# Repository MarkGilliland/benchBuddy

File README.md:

# benchBuddy
Code, schematics, and board layouts for the benchBuddy concept.

The benchBuddy is an adjustable power supply, DAQ unit, digital I/O source, and function generator! Just the thing for your workbench - your new buddy

Mark Gilliland 2019

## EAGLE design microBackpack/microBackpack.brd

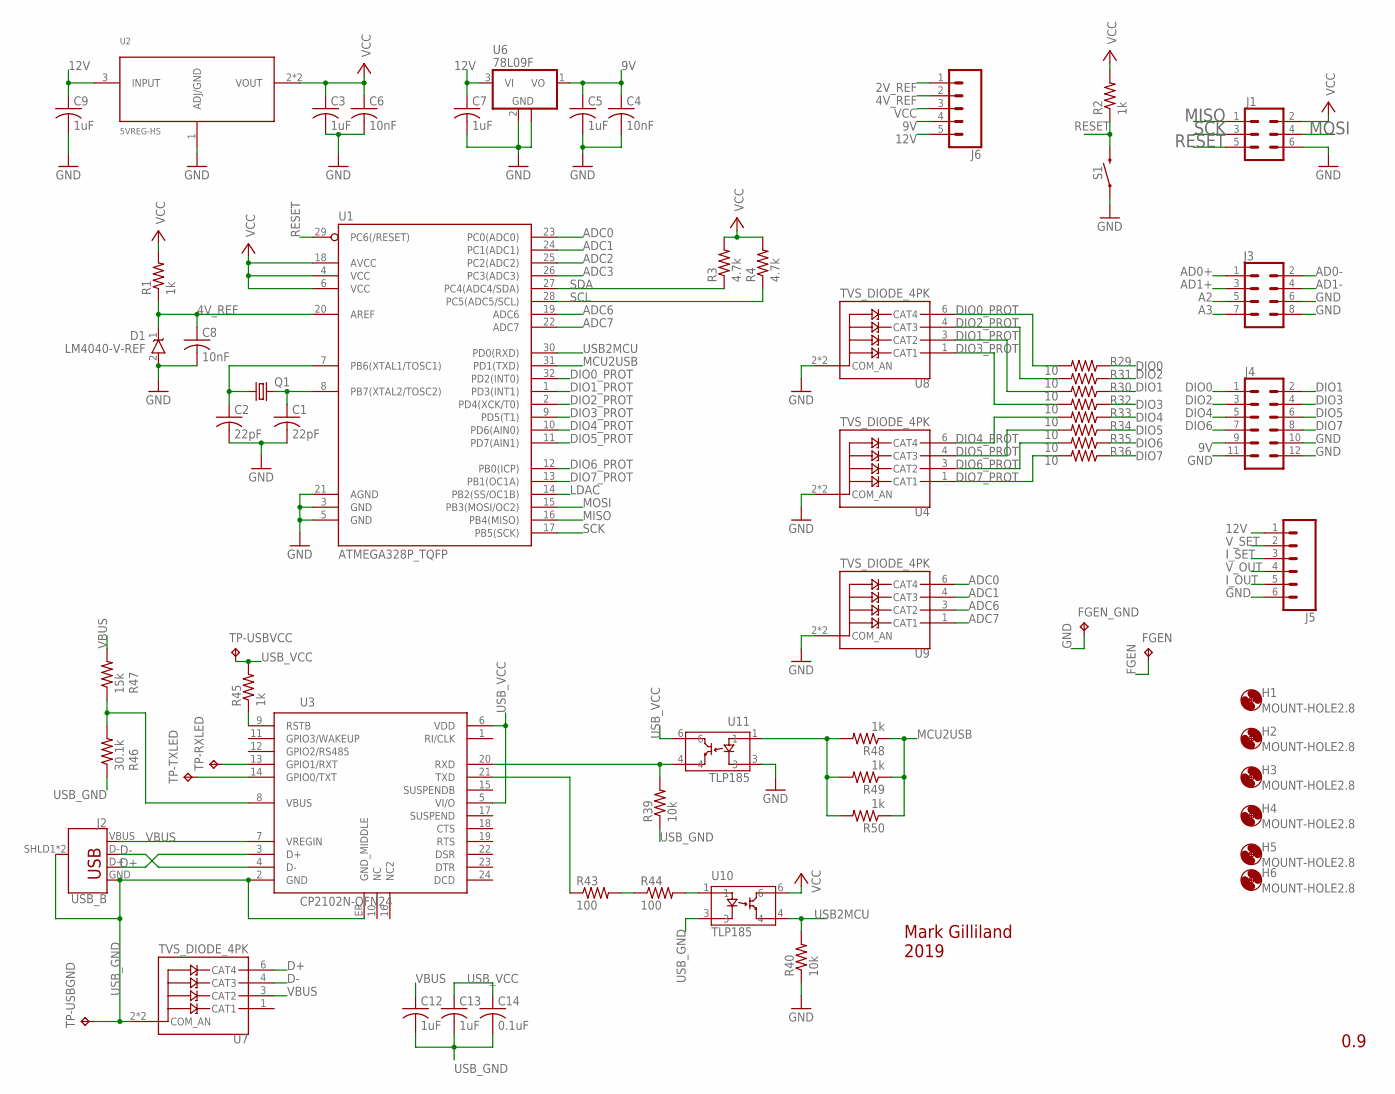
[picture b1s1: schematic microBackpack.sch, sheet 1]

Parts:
C1, C2: 22pF; C0805
C3, C5, C7, C9, C12, C13: 1uF; C0805
C4, C6, C8: 10nF; C0805
C14: 0.1uF; C0805
D1: LM4040-V-REF; SOT23
FGEN: TPPAD1-20Y; P1-20Y
FGEN_GND: TPPAD1-20Y; P1-20Y
H1, H2, H3, H4, H5, H6: MOUNT-HOLE2.8; 2,8
J1: CONN_03X22X3_SILK_MALE_PTH; 2X3
J2: USB_B; USB-B-PTH-VERT
J3: CONN_04X2; 2X4
J4: 2X6 FEMALE; 2X6
J5: CONN_06SILK_FEMALE_PTH; 1X06
J6: CONN_05NO_SILK; 1X05_NO_SILK
Q1: CRYSTALHC49U70; HC49U70
R1, R2, R45, R48, R49, R50: 1k; R0805
R3, R4: 4.7k; R0805
R29, R30, R31, R32, R33, R34, R35, R36: 10; R0805
R39, R40: 10k; R0805
R43, R44: 100; R0603
R46: 30.1k; R0805
R47: 15k; R0805
S1: MOMENTARY-SWITCH-SPST-SMD-5.2-REDUNDANT; TACTILE_SWITCH_SMD_5.2MM
TP-RXLED: TPPAD1-13; P1-13
TP-TXLED: TPPAD1-13; P1-13
TP-USBGND: TPPAD1-13; P1-13
TP-USBVCC: TPPAD1-13; P1-13
U1: ATMEGA328P_TQFP; TQFP32-08
U2: 5VREG-HS; SOT223-HS
U3: CP2102N-QFN24; QFN-24_ALT2
U4, U7, U8, U9: TVS_DIODE_4PK; SOT457
U6: 78L09F; SOT89
U10, U11: TLP185; SO06-4

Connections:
2V_REF: J6.1; also elsewhere on the board
4V_REF: C8.1, D1.1 (+IN), J6.2, R1.1, U1.20 (AREF); also elsewhere on the board
9V: C4.1, C5.1, J4.9, J6.4, U6.1 (VO); also elsewhere on the board
12V: C7.1, C9.1, J5.1, J6.5, U2.3 (INPUT), U6.3 (VI); also elsewhere on the board
A2: J3.5; also elsewhere on the board
A3: J3.7; also elsewhere on the board
AD0+: J3.1; also elsewhere on the board
AD0-: J3.2; also elsewhere on the board
AD1+: J3.3; also elsewhere on the board
AD1-: J3.4; also elsewhere on the board
ADC0: U1.23 (PC0(ADC0)), U9.6 (CAT4); also elsewhere on the board
ADC1: U1.24 (PC1(ADC1)), U9.4 (CAT3); also elsewhere on the board
ADC2: U1.25 (PC2(ADC2)); also elsewhere on the board
ADC3: U1.26 (PC3(ADC3)); also elsewhere on the board
ADC6: U1.19 (ADC6), U9.3 (CAT2); also elsewhere on the board
ADC7: U1.22 (ADC7), U9.1 (CAT1); also elsewhere on the board
CRYS_N: C2.1, Q1.1, U1.7 (PB6(XTAL1/TOSC1))
CRYS_P: C1.1, Q1.2, U1.8 (PB7(XTAL2/TOSC2))
D+: J2.D+, U3.3 (D+), U7.6 (CAT4)
D-: J2.D-, U3.4 (D-), U7.4 (CAT3)
DIO0: J4.1, R29.1
DIO0_PROT: R29.2, U1.32 (PD2(INT0)), U8.6 (CAT4)
DIO1: J4.2, R30.1
DIO1_PROT: R30.2, U1.1 (PD3(INT1)), U8.3 (CAT2)
DIO2: J4.3, R31.1
DIO2_PROT: R31.2, U1.2 (PD4(XCK/T0)), U8.4 (CAT3)
DIO3: J4.4, R32.1
DIO3_PROT: R32.2, U1.9 (PD5(T1)), U8.1 (CAT1)
DIO4: J4.5, R33.1
DIO4_PROT: R33.2, U1.10 (PD6(AIN0)), U4.6 (CAT4)
DIO5: J4.6, R34.1
DIO5_PROT: R34.2, U1.11 (PD7(AIN1)), U4.4 (CAT3)
DIO6: J4.7, R35.1
DIO6_PROT: R35.2, U1.12 (PB0(ICP)), U4.3 (CAT2)
DIO7: J4.8, R36.1
DIO7_PROT: R36.2, U1.13 (PB1(OC1A)), U4.1 (CAT1); also elsewhere on the board
FGEN: FGEN.TP; also elsewhere on the board
GND: C1.2, C2.2, C3.2, C4.2, C5.2, C6.2, C7.2, C8.2, C9.2, D1.2 (-IN), FGEN_GND.TP, J1.6, J3.6, J3.8, J4.10, J4.11, J4.12, J5.6, R40.1, S1.1, S1.2 (1), U1.3 (GND), U1.5 (GND), U1.21 (AGND), U2.1 (ADJ/GND), U4.2 (COM_AN), U4.5 (COM_AN), U6.2 (GND), U6.2@1 (GND), U8.2 (COM_AN), U8.5 (COM_AN), U9.2 (COM_AN), U9.5 (COM_AN), U11.3; also elsewhere on the board
I_OUT: J5.5; also elsewhere on the board
I_SET: J5.3; also elsewhere on the board
LDAC: U1.14 (PB2(SS/OC1B)); also elsewhere on the board
MCU2USB: R48.1, R49.1, R50.1, U1.31 (PD1(TXD))
MISO: J1.1, U1.16 (PB4(MISO))
MOSI: J1.4, U1.15 (PB3(MOSI/OC2))
unnamed: R48.2, R49.2, R50.2, U11.1
unnamed: R46.2, R47.1, U3.8 (VBUS)
unnamed: R44.2, U10.1
unnamed: R39.2, U3.20 (RXD), U11.4
unnamed: R43.2, R44.1
unnamed: R43.1, U3.21 (TXD)
unnamed: TP-RXLED.TP, U3.13 (GPIO1/RXT)
unnamed: TP-TXLED.TP, U3.14 (GPIO0/TXT)
unnamed: R45.1, U3.9 (RSTB)
RESET: J1.5, R2.1, S1.3 (2), S1.4 (2), U1.29 (PC6(/RESET))
SCK: J1.3, U1.17 (PB5(SCK))
SCL: R4.1, U1.28 (PC5(ADC5/SCL)); also elsewhere on the board
SDA: R3.1, U1.27 (PC4(ADC4/SDA)); also elsewhere on the board
USB2MCU: R40.2, U1.30 (PD0(RXD)), U10.4
USB_GND: C12.2, C13.2, C14.2, J2.GND, J2.SHLD1 (SHIELD), J2.SHLD2 (SHIELD), R39.1, R46.1, TP-USBGND.TP, U3.2 (GND), U3.EP (GND_MIDDLE), U7.2 (COM_AN), U7.5 (COM_AN), U10.3
USB_VCC: C13.1, C14.1, R45.2, TP-USBVCC.TP, U3.5 (VI/O), U3.6 (VDD), U11.6
VBUS: C12.1, J2.VBUS, R47.2, U3.7 (VREGIN), U7.3 (CAT2)
VCC: C3.1, C6.1, J1.2, J6.3, R1.2, R2.2, R3.2, R4.2, U1.4 (VCC), U1.6 (VCC), U1.18 (AVCC), U2.2 (VOUT), U2.4 (VOUT), U10.6; also elsewhere on the board
V_OUT: J5.4; also elsewhere on the board
V_SET: J5.2; also elsewhere on the board

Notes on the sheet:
Mark Gilliland 2019
0.9

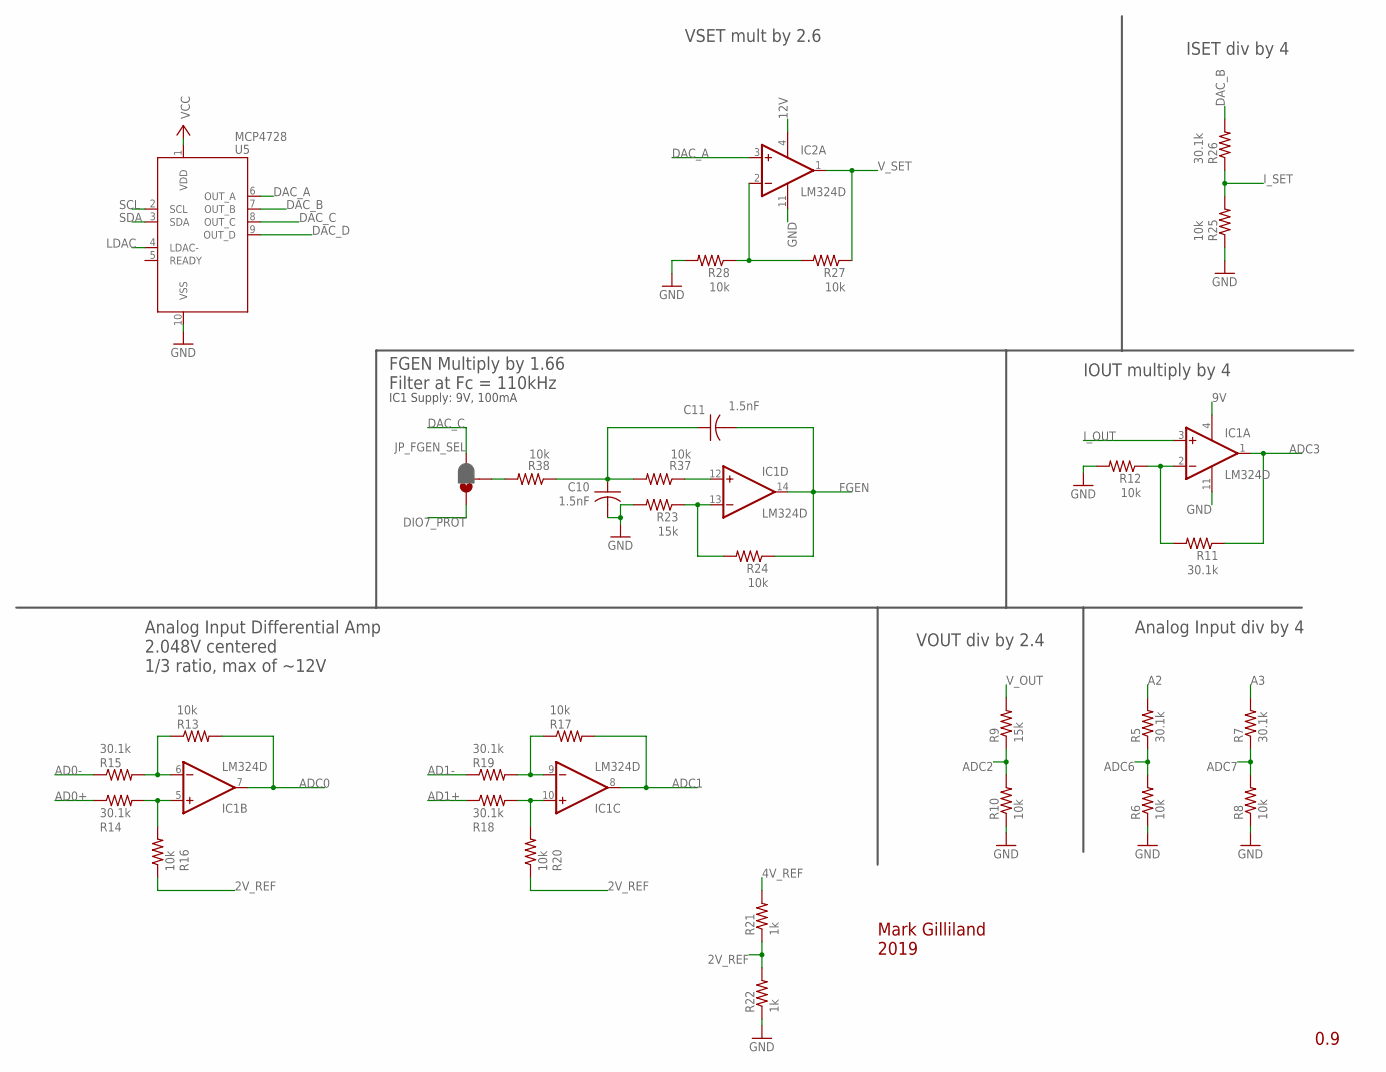
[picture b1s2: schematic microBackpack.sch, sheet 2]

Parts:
C10, C11: 1.5nF; C0805
IC1, IC2: LM324D; SO14
JP_FGEN_SEL: JUMPER-SMT_3_1-NC_PASTE_SILK; SMT-JUMPER_3_1-NC_PASTE_SILK
R5, R7, R11, R14, R15, R18, R19, R26: 30.1k; R0805
R6, R8, R10, R12, R13, R16, R17, R20, R24, R25, R27, R28, R37, R38: 10k; R0805
R9, R23: 15k; R0805
R21, R22: 1k; R0805
U5: MCP4728; MSOP10

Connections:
2V_REF: R16.1, R20.1, R21.1, R22.2; also elsewhere on the board
4V_REF: R21.2; also elsewhere on the board
9V: IC1.4 (V+); also elsewhere on the board
12V: IC2.4 (V+); also elsewhere on the board
A2: R5.2; also elsewhere on the board
A3: R7.2; also elsewhere on the board
AD0+: R14.1; also elsewhere on the board
AD0-: R15.1; also elsewhere on the board
AD1+: R18.1; also elsewhere on the board
AD1-: R19.1; also elsewhere on the board
ADC0: IC1.7 (OUT), R13.2; also elsewhere on the board
ADC1: IC1.8 (OUT), R17.2; also elsewhere on the board
ADC2: R9.1, R10.2; also elsewhere on the board
ADC3: IC1.1 (OUT), R11.1; also elsewhere on the board
ADC6: R5.1, R6.2; also elsewhere on the board
ADC7: R7.1, R8.2; also elsewhere on the board
DAC_A: IC2.3 (+IN), U5.6 (OUT_A)
DAC_B: R26.2, U5.7 (OUT_B)
DAC_C: JP_FGEN_SEL.3, U5.8 (OUT_C)
DAC_D: U5.9 (OUT_D)
DIO7_PROT: JP_FGEN_SEL.1; also elsewhere on the board
FGEN: C11.2, IC1.14 (OUT), R24.1; also elsewhere on the board
GND: C10.2, IC1.11 (V-), IC2.11 (V-), R6.1, R8.1, R10.1, R12.2, R22.1, R23.2, R25.1, R28.2, U5.10 (VSS); also elsewhere on the board
I_OUT: IC1.3 (+IN); also elsewhere on the board
I_SET: R25.2, R26.1; also elsewhere on the board
LDAC: U5.4 (LDAC-); also elsewhere on the board
unnamed: JP_FGEN_SEL.2, R38.2
unnamed: IC1.13 (-IN), R23.1, R24.2
unnamed: C10.1, C11.1, R37.2, R38.1
unnamed: IC1.2 (-IN), R11.2, R12.1
unnamed: IC1.6 (-IN), R13.1, R15.2
unnamed: IC1.5 (+IN), R14.2, R16.2
unnamed: IC2.2 (-IN), R27.2, R28.1
unnamed: IC1.12 (+IN), R37.1
unnamed: IC1.9 (-IN), R17.1, R19.2
unnamed: IC1.10 (+IN), R18.2, R20.2
SCL: U5.2 (SCL); also elsewhere on the board
SDA: U5.3 (SDA); also elsewhere on the board
VCC: U5.1 (VDD); also elsewhere on the board
V_OUT: R9.2; also elsewhere on the board
V_SET: IC2.1 (OUT), R27.1; also elsewhere on the board

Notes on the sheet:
Mark Gilliland 2019
0.9
VOUT div by 2.4
IOUT multiply by 4
Analog Input div by 4
Analog Input Differential Amp 2.048V centered 1/3 ratio, max of ~12V
FGEN Multiply by 1.66 Filter at Fc = 110kHz
IC1 Supply: 9V, 100mA
ISET div by 4
VSET mult by 2.6

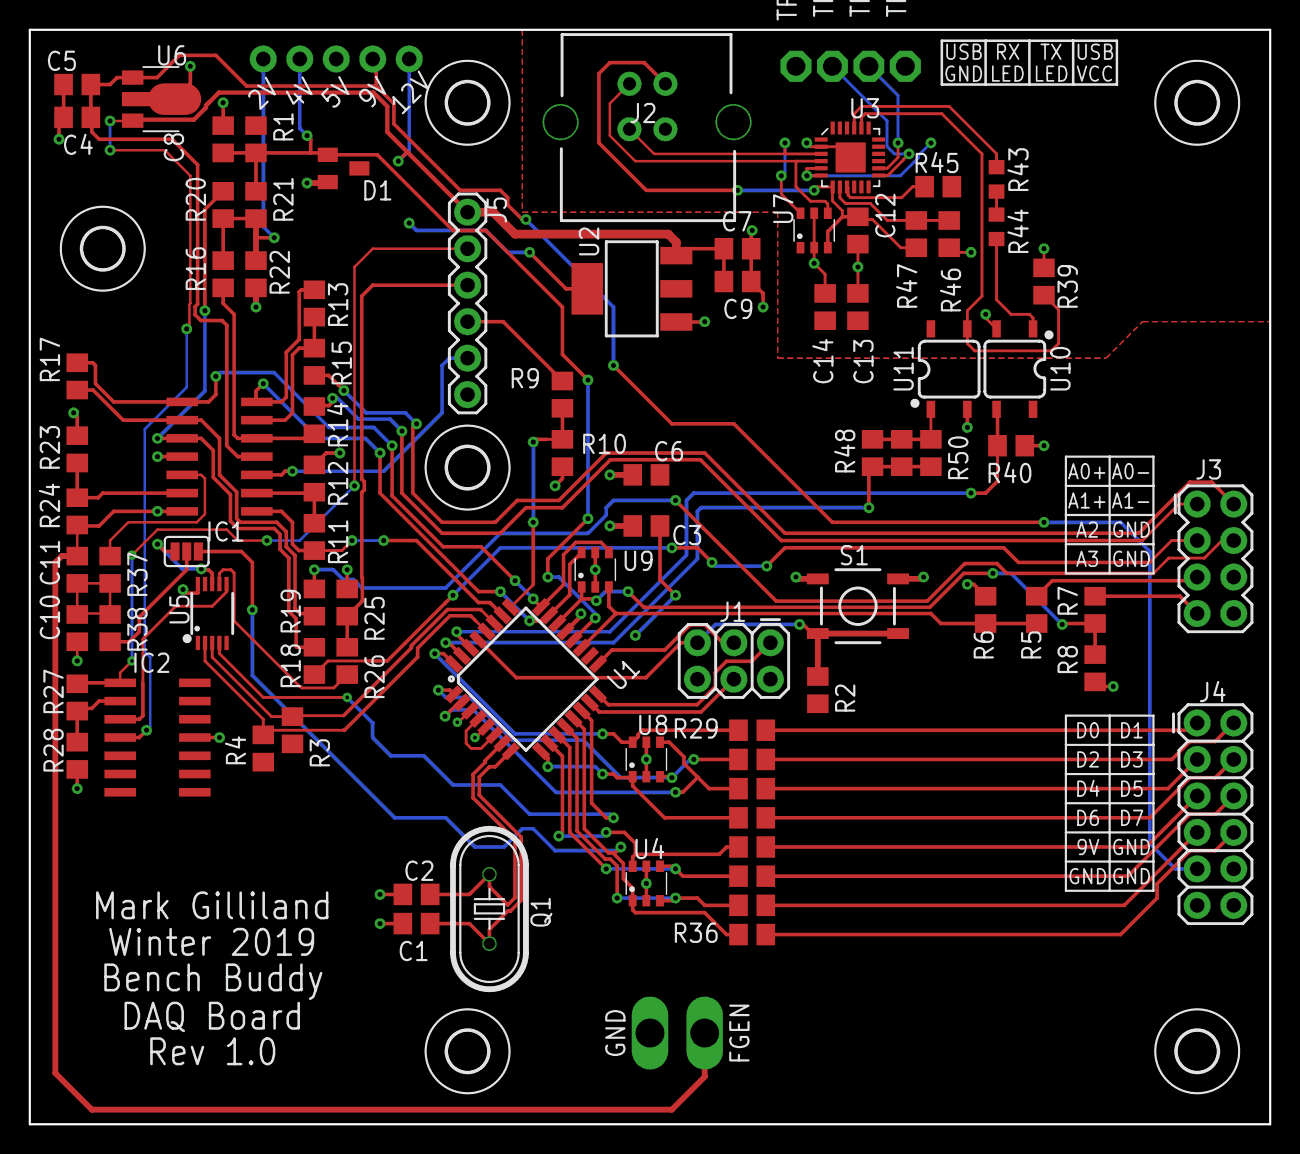
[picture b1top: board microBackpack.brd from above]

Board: 2 copper layers, 86.4 x 76.2 mm, 97 parts (0 on the bottom side), 77 nets.

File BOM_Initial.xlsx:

Usage | Component Type | RefDes | Value | Package | Description | Part Number 1 | Part Number 2 | Link | Qty Required | Order Qty | Price Per | Price | Board | Part List
Crystal Capacitors | Passive, Capacitor | C1, C2 | 22pF | C0805 | CAP CER 22PF 16V C0G/NP0 0805 | 732-7816-1-ND |  | 732-7816-1-ND | 2 | 10 | 4.2999999999999997E-2 | 8.5999999999999993E-2 | MBP | MBP-C1, C2
FGen Filter Caps | Passive, Capacitor | C10, C11 | 1.5nF | C0805 | CAP CER 1500PF 25V NP0 0805 | 732-12256-1-ND |  | 732-12256-1-ND | 2 | 2 | 0.1 | 0.2 | MBP | MBP-C10, C11
Power Filter Caps | Passive, Capacitor | C3, C5, C7, C9 | 1uF | C0805 |  | 1276-6471-1-ND |  | 1276-6471-1-ND | 4 | 10 | 4.7E-2 | 0.188 | MBP | MBP-C3, C5, C7, C9
Power Filter Caps | Passive, Capacitor | C4, C6, C8 | 10nF | C0805 |  | ‎732-8074-1-ND‎ |  | ‎732-8074-1-ND‎ | 3 | 10 | 3.4000000000000002E-2 | 0.10200000000000001 | MBP | MBP-C4, C6, C8
Filter Cap, HF | Passive, Capacitor | C8, C11, C13 | 0.1uF | C0805 |  | 1276-1007-1-ND |  | 1276-1007-1-ND | 3 | 10 | 0.04 | 0.12 | PSB | PSB-C8, C11, C13
Filter Cap, LF | Passive, Capacitor | C9, C10, C12, C14 | 10uF | C0805 |  | 1276-6455-1-ND |  | 1276-6455-1-ND | 4 | 10 | 0.108 | 0.432 | PSB | PSB-C9, C10, C12, C14
Voltage Reference | Diode | D1 | SOT-23-3 |  |  | 576-1048-1-ND |  | 576-1048-1-ND | 1 | 1 | 0.28999999999999998 | 0.28999999999999998 | MBP | MBP-D1
4A Fuse for 12V | Fuse, PTC | F1 |  | F1812 | PTC RESET FUSE 16V 2.6A 1812 | 507-1780-1-ND |  | 507-1780-1-ND | 1 | 2 | 0.28000000000000003 | 0.28000000000000003 | PSB | PSB-F1
750mA Fuse for 3.3 and 5V | Fuse, PTC | F2, F3 |  | F1812 | PTC RESET FUSE 16V 500MA 1812 | 507-1761-1-ND |  | 507-1761-1-ND | 2 | 3 | 0.14000000000000001 | 0.28000000000000003 | PSB | PSB-F2, F3
1A Fuse for 3.3 and 5V, alternate part | Fuse, PTC | F2, F3 |  | F1812 | PTC RESET FUSE 16V 750MA 1812 | 507-1763-1-ND |  | 507-1763-1-ND | 2 | 3 | 0.14000000000000001 | 0.28000000000000003 | PSB | PSB-F2, F3
Op Amp for AINs | IC, Linear | IC1, IC2 | SO14 |  |  | LM324DR2GOSCT-ND |  | LM324DR2GOSCT-ND | 2 | 2 | 0.35 | 0.7 | MBP | MBP-IC1, IC2
ICSP Header | Header | J1 |  |  | 2x3 0.1" header, for flashing the bootloader to the atmega | 2057-PH2-06-UA-ND |  | 2057-PH2-06-UA-ND | 1 | 1 | 0.12 | 0.12 | MBP | MBP-J1
USB Port | Header | J2 |  |  | USB TYPE B, RIGHT ANGLE, WHITE C | 2057-USB-B-S-RA-WT-SPCC-ND |  | 2057-USB-B-S-RA-WT-SPCC-ND | 1 | 1 | 0.45 | 0.45 | MBP | MBP-J2
USB Port, Vertical | Header | J2 |  |  | CONN RCPT USB2.0 TYPEB 4POS VERT | 102-4000-ND |  | 102-4000-ND | 1 | 1 | 0.75 | 0.75 | MBP | MBP-J2
Expansion Header, Male | Header | J3 |  | 1x6x0.1" |  | 2057-PH1-06-UA-ND |  | 2057-PH1-06-UA-ND | 1 | 1 | 0.12 | 0.12 | PSB | PSB-J3
Output Header, DIO | Header | J4, J3 |  |  | 6x2 header, 0.1", for digitals | 2057-PH2-12-UA-ND |  | 2057-PH2-12-UA-ND | 2 | 2 | 0.18 | 0.36 | MBP | MBP-J4, J3
Expansion Header, Female | Header | J5 |  | 1x6x0.1" |  | S7039-ND |  | S7039-ND | 1 | 1 | 0.53 | 0.53 | MBP | MBP-J5
UART Optoisolator | IC, Logic | NA | 6-SOIC |  |  | TLP185(GB-TPLSECT-ND |  | TLP185(GB-TPLSECT-ND | 2 | 2 | 0.42 | 0.84 | MBP | MBP-NA
5W 5V Switch Mode Reg | IC, DCDC Converter | PS1, PS2 |  | 3-SIP Module | 5V 1.0A DC-DC NON-ISOLATED | 102-5018-ND |  | 102-5018-ND | 2 | 2 | 2.96 | 5.92 | PSB | PSB-PS1, PS2
Crystal Oscillator | Crystal | Q1 |  | HC-49 | 16MHz | 887-2015-ND |  | 887-2015-ND | 1 | 1 | 0.3 | 0.3 | MBP | MBP-Q1
Vref Resistor | Passive, Resistor | R1, R2, R21, R22 | 1k | R0805 | RES 1K OHM 1% 1/8W 0805 | RMCF0805FT1K00CT-ND |  | RMCF0805FT1K00CT-ND | 4 | 10 | 2.7E-2 | 0.108 | MBP | MBP-R1, R2, R21, R22
DIO Protection resistors | Passive, Resistor | R29, R30, R31, R32, R33, R34, R35, R36 | 10 | R0805 | RES SMD 10 OHM 5% 1/8W 0805 | CR0805-JW-100ELFCT-ND |  | CR0805-JW-100ELFCT-ND | 8 | 10 | 1.7999999999999999E-2 | 0.14399999999999999 | MBP | MBP-R29, R30, R31, R32, R33, R34, R35, R36
I2C Pull-ups | Passive, Resistor | R3, R4 | 4.7k | R0805 | RES SMD 4.7K OHM 5% 1/8W 0805 | CR0805-JW-472ELFCT-ND |  | CR0805-JW-472ELFCT-ND | 2 | 10 | 1.7999999999999999E-2 | 3.5999999999999997E-2 | MBP | MBP-R3, R4
12V LED Resistor | Passive, Resistor | R31 | 1.2k | R1206 | RES 1.2K OHM 5% 1/4W 1206 | RMCF1206JT1K20CT-ND |  | RMCF1206JT1K20CT-ND | 1 | 1 | 0.1 | 0.1 | PSB | PSB-R31
5V LED Resistor | Passive, Resistor | R32 | 390Ω | R1206 | RES 390 OHM 5% 1/4W 1206 | RMCF1206JT390RCT-ND |  | RMCF1206JT390RCT-ND | 1 | 1 | 0.1 | 0.1 | PSB | PSB-R32
3.3V LED Resistor | Passive, Resistor | R33 | 150Ω | R1206 | RES 150 OHM 5% 1/4W 1206 | RMCF1206JT150RCT-ND |  | RMCF1206JT150RCT-ND | 1 | 1 | 0.1 | 0.1 | PSB | PSB-R33
Amp Resistors | Passive, Resistor | R5, R7, R11, R14, R15, R18, R19, R26 | 30.1k 1% | R0805 | RES 30.1K OHM 1% 1/8W 0805 | RMCF0805FT30K1CT-ND |  | RMCF0805FT30K1CT-ND | 8 | 10 | 2.7E-2 | 0.216 | MBP | MBP-R5, R7, R11, R14, R15, R18, R19, R26
Amp Resistors | Passive, Resistor | R6, R8, R10, R12, R13, R16, R17, R20, R24, R25, R27, R28, R37, R38 | 10k 1% | R0805 | RES 10K OHM 1% 1/8W 0805 | RMCF0805FT10K0CT-ND |  | RMCF0805FT10K0CT-ND | 14 | 100 | 2.7E-2 | 0.378 | MBP | MBP-R6, R8, R10, R12, R13, R16, R17, R20, R24, R25, R27, R28, R37, R38
Amp Resistors | Passive, Resistor | R9, R23 | 15k 1% | R0805 | RES 15K OHM 1% 1/8W 0805 | RMCF0805FT15K0CT-ND |  | RMCF0805FT15K0CT-ND | 2 | 10 | 2.7E-2 | 5.3999999999999999E-2 | MBP | MBP-R9, R23
Reset button | Button | S1 |  | 5.2mm sqaure | TACT 5.2 X 5.2, 1.5 MM H, 160GF, | CKN12220-1-ND |  | CKN12220-1-ND | 1 | 1 | 0.1 | 0.1 | MBP | MBP-S1
Selection Switch | Switch | S3 |  |  | Made to match ones from class | 401-2001-ND |  | 401-2001-ND | 1 | 1 | 0.43 | 0.43 | PSB | PSB-S3
Microcontroller, Arduino | IC, Logic | U1 |  | 32-TQFP |  | ATMEGA328PB-AURCT-ND | ATMega328P | ATMEGA328PB-AURCT-ND | 1 | 1 | 1.42 | 1.42 | MBP | MBP-U1
5V Supply | IC, Linear | U2 |  | SOT223 | IC REG LINEAR 5V 800MA SOT223 | AZ1117IH-5.0TRG1DICT-ND |  | AZ1117IH-5.0TRG1DICT-ND | 1 | 3 | 0.36 | 0.36 | MBP | MBP-U2
1A 3.3V Linear Reg | IC, Volt Reg | U3 |  | SOT223 | IC REG LINEAR 3.3V 1A SOT223 | AP2114HA-3.3TRG1DICT-ND |  | AP2114HA-3.3TRG1DICT-ND | 1 | 3 | 0.36 | 0.36 | PSB | PSB-U3
USB to UART Adapter | IC, Logic | U3 |  |  | CP2102N-A02-GQFN24R | 336-5888-1-ND |  | 336-5888-1-ND | 1 | 1 | 1.35 | 1.35 | MBP | MBP-U3
5V/AIN/USB protection diodes | Diode | U4, U7, U8, U9 |  |  |  | 1727-1582-1-ND |  | 1727-1582-1-ND | 4 | 5 | 0.31 | 1.24 | MBP | MBP-U4, U7, U8, U9
Op Amp Power Supply | IC, Linear | U6 | SOT89-3 |  | IC REG LINEAR 9V 100MA SOT89-3 | 497-1192-1-ND | L78L09ACUTR | 497-1192-1-ND | 1 | 1 | 0.4 | 0.4 | MBP | MBP-U6
 |  |  |  |  |  |  |  |  |  |  | Total: | 19.244

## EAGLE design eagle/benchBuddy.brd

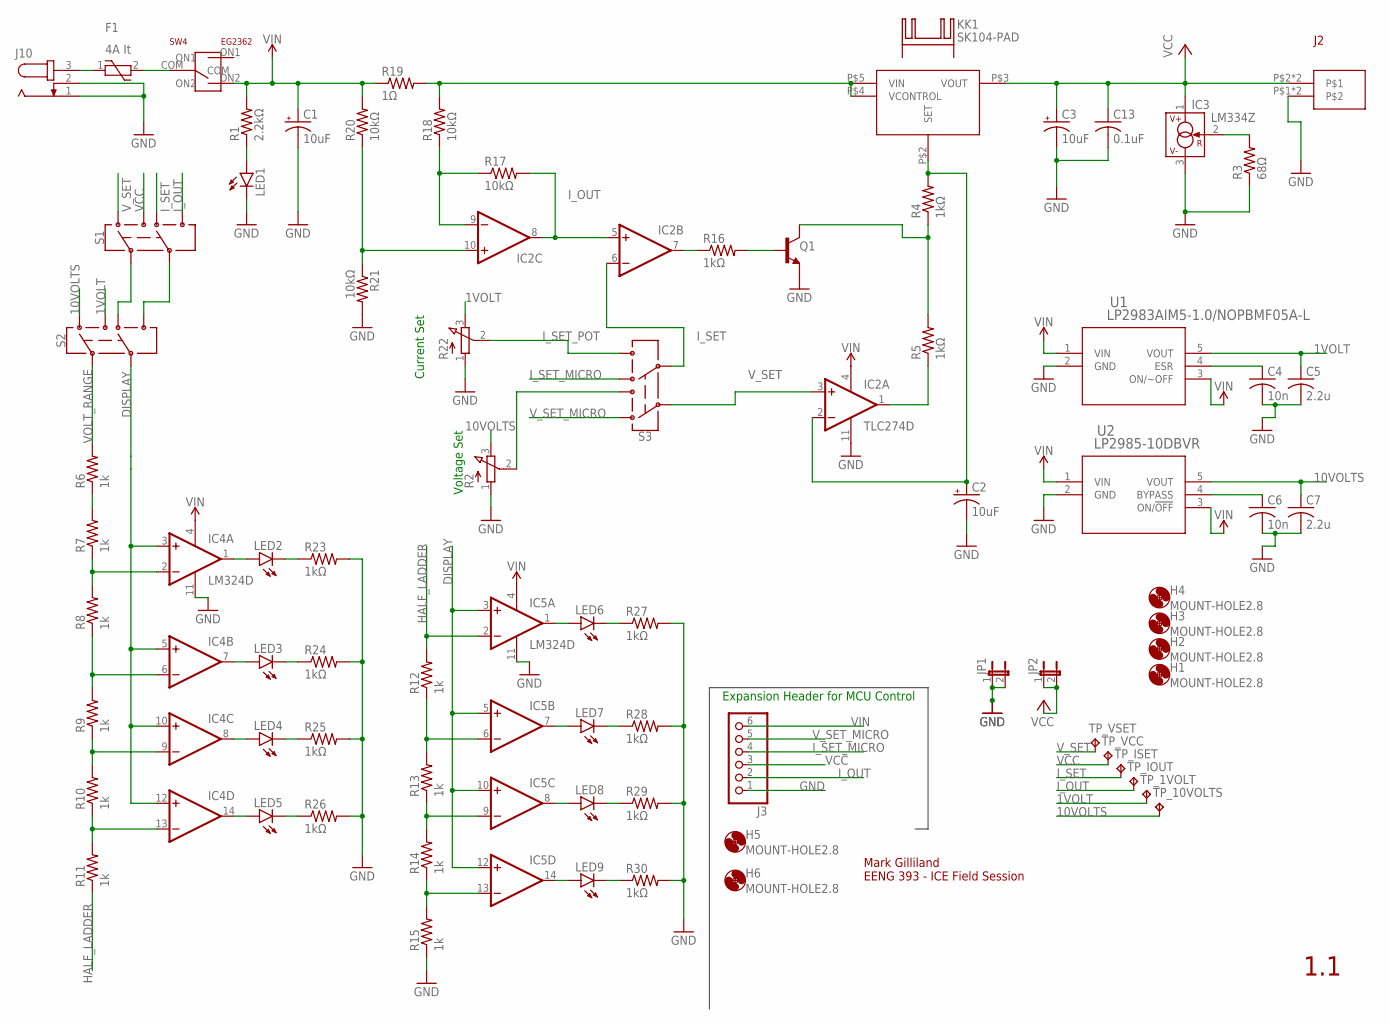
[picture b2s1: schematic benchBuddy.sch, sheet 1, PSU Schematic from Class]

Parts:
C1, C2, C3: 10uF; PANASONIC_B
C4, C6: 10n; C1206
C5, C7: 2.2u; C1206
C13: 0.1uF; C0805
F1: 4A It; LITTELFUSE_MINISMDC260F/12-2
H1, H2, H3, H4, H5, H6: MOUNT-HOLE2.8; 2,8
IC2: TLC274D; SO14
IC3: LM334Z; TO92
IC4, IC5: LM324D; SO14
J2: PHOENIX_SPRING_TERM_2POS; SPRING_TERM_2POS
J3: PINHD-1X6; 1X06
J10: JACK-PLUG0; SPC4077
JP1, JP2: JP1E; JP1
KK1: SK104-PAD
LED1, LED2, LED3, LED4, LED5, LED6, LED7, LED8, LED9: LEDCHIPLED_1206; CHIPLED_1206
Q1: 600mA/40V; SOT23-3
R1: 2.2kΩ; R1206
R2, R22: EVUF2A; EVUF
R3: 68Ω; R1206
R4, R5, R16, R23, R24, R25, R26, R27, R28, R29, R30: 1kΩ; R1206
R6, R7, R8, R9, R10, R11, R12, R13, R14, R15: 1k; R1206
R17, R18, R20, R21: 10kΩ; R1206
R19: 1Ω; 0411/15
S1, S2, S3: SWITCH-DPDT-SMD-AYZ0202; SWITCH_DPDT_SMD_AYZ0202
SW4: EG2362; SWITCH_EG2362-ND
TP_1VOLT, TP_10VOLTS: TPB1,27; B1,27
TP_IOUT: TPB1,27; B1,27
TP_ISET: TPB1,27; B1,27
TP_VCC: TPB1,27; B1,27
TP_VSET: TPB1,27; B1,27
U1: LP2983AIM5-1.0/NOPBMF05A-L; MF05A-L
U2: LP2985-10DBVR; DBV5
U$1: LT3080; TO-220-5R

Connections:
1VOLT: C5.1, R22.3 (E), S2.3, TP_1VOLT.TP, U1.5 (VOUT); also elsewhere on the board
10VOLTS: C7.1, R2.3 (E), S2.1, TP_10VOLTS.TP, U2.5 (VOUT); also elsewhere on the board
DISPLAY: IC4.3 (+IN), IC4.5 (+IN), IC4.10 (+IN), IC4.12 (+IN), IC5.3 (+IN), IC5.5 (+IN), IC5.10 (+IN), IC5.12 (+IN), S2.5
GND: C1.-, C2.-, C3.-, C4.2, C5.2, C6.2, C7.2, C13.2, IC2.11 (V-), IC3.3 (V-), IC4.11 (V-), IC5.11 (V-), J2.P$1, J2.P$3, J3.1, J10.1, J10.2, JP1.1, JP1.2, LED1.C, Q1.2 (E), R2.1 (A), R3.1, R15.1, R21.2, R22.1 (A), R23.2, R24.2, R25.2, R26.2, R27.2, R28.2, R29.2, R30.2, U1.2 (GND), U2.2 (GND); also elsewhere on the board
HALF_LADDER: IC5.2 (-IN), R11.1, R12.2
I_OUT: IC2.5 (+IN), IC2.8 (OUT), J3.2, R17.2, S1.6, TP_IOUT.TP; also elsewhere on the board
I_SET: IC2.6 (-IN), S1.4, S3.5, TP_ISET.TP; also elsewhere on the board
I_SET_MICRO: J3.4, S3.4
I_SET_POT: R22.2 (S), S3.6
unnamed: LED1.A, R1.1
unnamed: IC3.2 (R), R3.2
unnamed: F1.1, J10.3
unnamed: Q1.3 (C), R4.1, R5.2
unnamed: C2.+, IC2.2 (-IN), R4.2, U$1.P$2 (SET)
unnamed: R6.1, R7.2
unnamed: IC5.13 (-IN), R14.1, R15.2
unnamed: IC5.9 (-IN), R13.1, R14.2
unnamed: IC5.6 (-IN), R12.1, R13.2
unnamed: IC4.2 (-IN), R7.1, R8.2
unnamed: IC4.6 (-IN), R8.1, R9.2
unnamed: IC4.9 (-IN), R9.1, R10.2
unnamed: IC4.13 (-IN), R10.1, R11.2
unnamed: IC2.10 (+IN), R20.1, R21.1
unnamed: IC2.9 (-IN), R17.1, R18.1
unnamed: R18.2, R19.2, U$1.P$4 (VCONTROL), U$1.P$5 (VIN)
unnamed: C6.1, U2.4 (BYPASS)
unnamed: IC2.7 (OUT), R16.1
unnamed: Q1.1 (B), R16.2
unnamed: IC4.1 (OUT), LED2.A
unnamed: LED2.C, R23.1
unnamed: LED3.C, R24.1
unnamed: LED4.C, R25.1
unnamed: LED5.C, R26.1
unnamed: LED6.C, R27.1
unnamed: LED7.C, R28.1
unnamed: LED8.C, R29.1
unnamed: LED9.C, R30.1
unnamed: IC5.1 (OUT), LED6.A
unnamed: IC5.7 (OUT), LED7.A
unnamed: IC5.8 (OUT), LED8.A
unnamed: IC5.14 (OUT), LED9.A
unnamed: C4.1, U1.4 (ESR)
unnamed: S1.2, S2.4
unnamed: S1.5, S2.6
unnamed: F1.2, SW4.COM
unnamed: IC4.7 (OUT), LED3.A
unnamed: IC4.8 (OUT), LED4.A
unnamed: IC4.14 (OUT), LED5.A
ON1: SW4.ON1
VCC: C3.+, C13.1, IC3.1 (V+), J2.P$2, J2.P$4, J3.3, JP2.1, JP2.2, S1.3, TP_VCC.TP, U$1.P$3 (VOUT); also elsewhere on the board
VIN: C1.+, IC2.4 (V+), IC4.4 (V+), IC5.4 (V+), J3.6, R1.2, R19.1, R20.2, SW4.ON2, U1.1 (VIN), U1.3 (ON/~OFF), U2.1 (VIN), U2.3 (ON/!OFF); also elsewhere on the board
VOLT_RANGE: R6.2, S2.2
V_OUT: IC2.1 (OUT), R5.1
V_SET: IC2.3 (+IN), S1.1, S3.2, TP_VSET.TP; also elsewhere on the board
V_SET_MICRO: J3.5, S3.1
V_SET_POT: R2.2 (S), S3.3

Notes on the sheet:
Mark Gilliland EENG 393 - ICE Field Session
Voltage Set
Current Set
1.1
Expansion Header for MCU Control

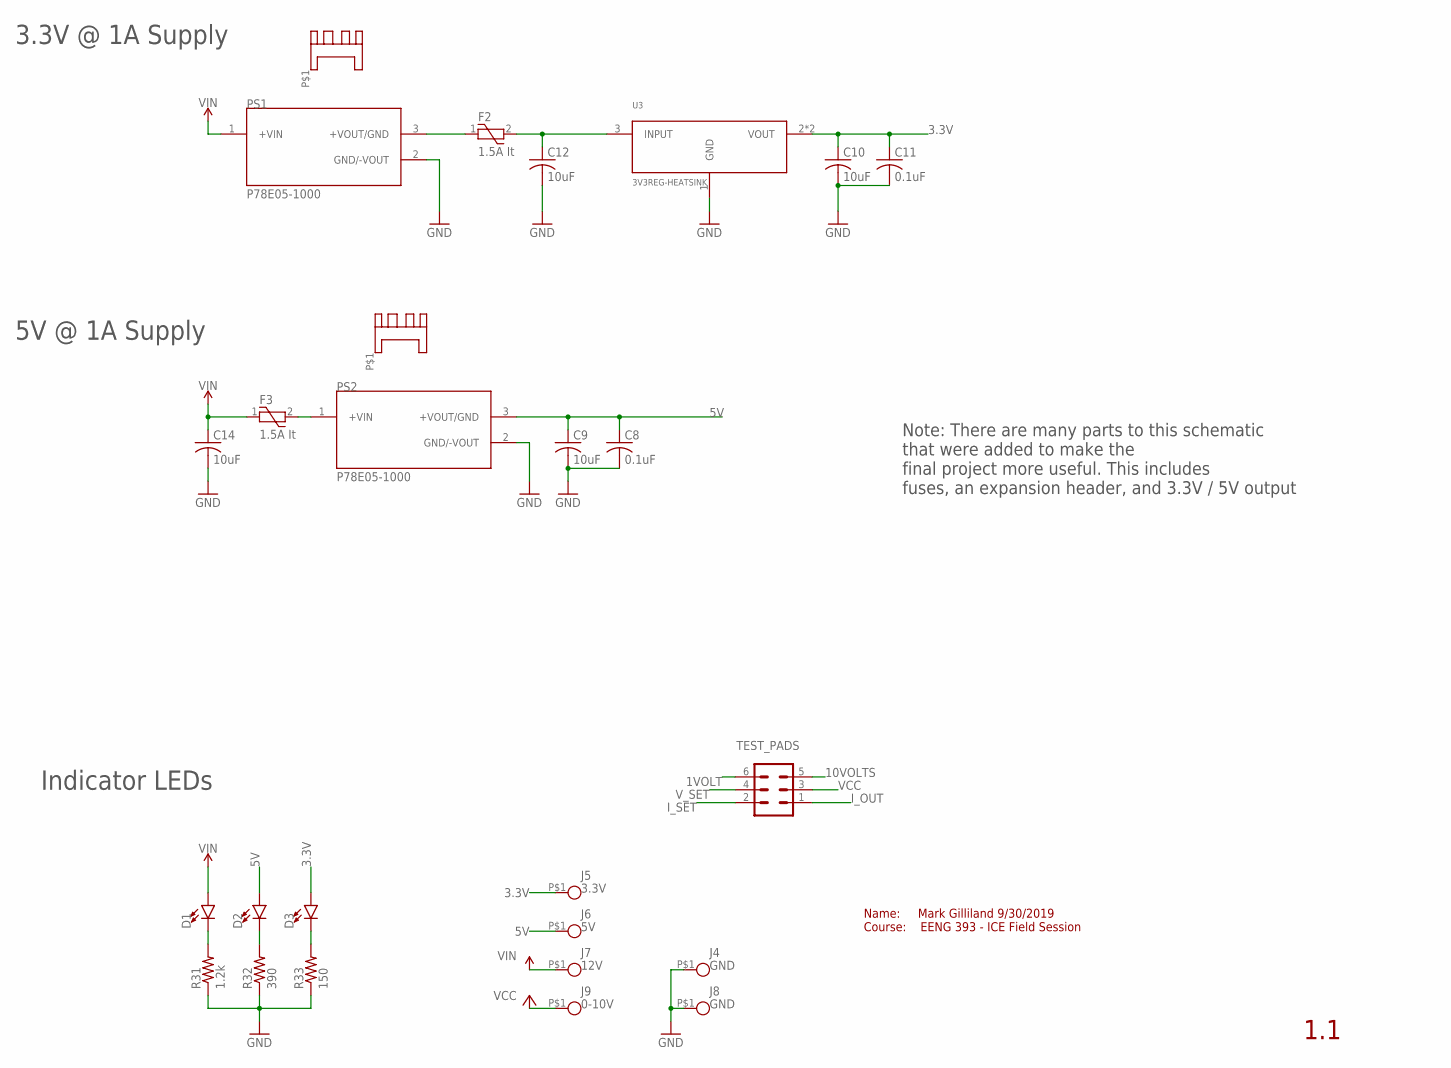
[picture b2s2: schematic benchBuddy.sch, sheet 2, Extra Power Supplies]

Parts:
C8, C11: 0.1uF; C0805
C9, C10, C12, C14: 10uF; C0805
D1, D2, D3: LED3MM; LED_3MM
F2, F3: 1.5A It; LITTELFUSE_MINISMDC260F/12-2
J4, J8: GND; FAT-PAD
J5: 3.3V; FAT-PAD
J6: 5V; FAT-PAD
J7: 12V; FAT-PAD
J9: 0-10V; FAT-PAD
PS1, PS2: P78E05-1000; CONV_P78E05-1000
R31: 1.2k; R1206
R32: 390; R1206
R33: 150; R1206
TEST_PADS: CONN_03X2NO_SILK; 2X3-NS
U3: 3V3REG-HEATSINK; SOT223-HS
U$2, U$3: HEATSINK_MINI

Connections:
1VOLT: TEST_PADS.6; also elsewhere on the board
3.3V: C10.1, C11.1, D3.A, J5.P$1, U3.2 (VOUT), U3.4 (VOUT)
5V: C8.1, C9.1, D2.A, J6.P$1, PS2.3 (+VOUT/GND)
10VOLTS: TEST_PADS.5; also elsewhere on the board
GND: C8.2, C9.2, C10.2, C11.2, C12.2, C14.2, J4.P$1, J8.P$1, PS1.2 (GND/-VOUT), PS2.2 (GND/-VOUT), R31.1, R32.1, R33.1, U3.1 (GND); also elsewhere on the board
I_OUT: TEST_PADS.1; also elsewhere on the board
I_SET: TEST_PADS.2; also elsewhere on the board
unnamed: F3.2, PS2.1 (+VIN)
unnamed: D1.K (C), R31.2
unnamed: D2.K (C), R32.2
unnamed: D3.K (C), R33.2
unnamed: F2.1, PS1.3 (+VOUT/GND)
unnamed: C12.1, F2.2, U3.3 (INPUT)
VCC: J9.P$1, TEST_PADS.3; also elsewhere on the board
VIN: C14.1, D1.A, F3.1, J7.P$1, PS1.1 (+VIN); also elsewhere on the board
V_SET: TEST_PADS.4; also elsewhere on the board

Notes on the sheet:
Name: Mark Gilliland 9/30/2019 Course: EENG 393 - ICE Field Session
3.3V @ 1A Supply
5V @ 1A Supply
Indicator LEDs
1.1
Note: There are many parts to this schematic that were added to make the final project more useful. This includes fuses, an expansion header, and 3.3V / 5V output

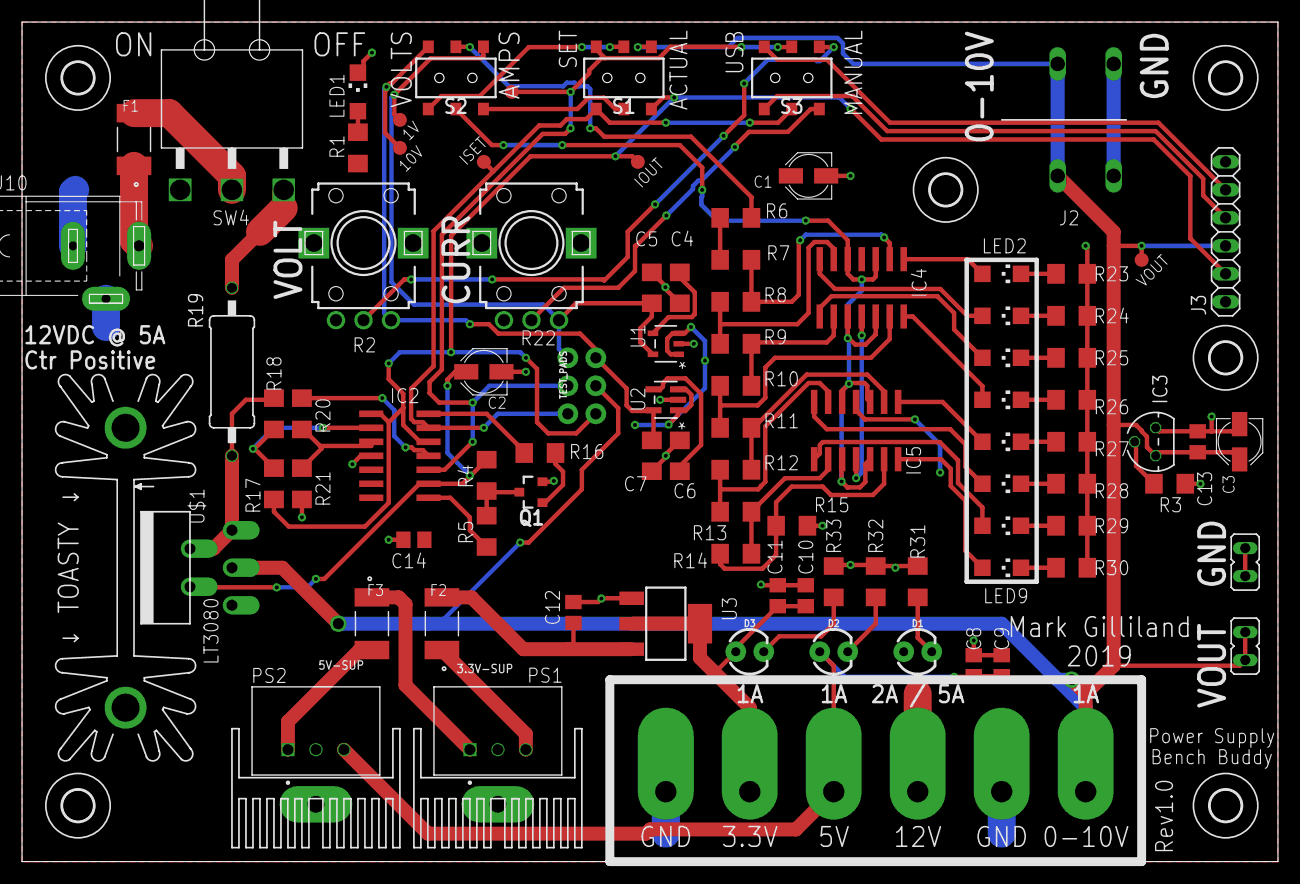
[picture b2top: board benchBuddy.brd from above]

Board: 2 copper layers, 114.0 x 76.2 mm, 104 parts (0 on the bottom side), 63 nets.

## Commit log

2019-10-27 Added Readme and gitignore
2019-10-27 Added in brd and sch files, ready to start
2019-10-27 Added all parts. Schematic finished. Consider Rev 1.0
2019-10-27 Basic dimensions and mechanical layout of board
2019-10-27 More detailed board layout. Began LED and VU layout
2019-10-27 Most components in final position
2019-10-27 VU meter routed
2019-10-27 Added mini heatsinks for T220 Packages. Also more work on layout
2019-10-28 Board mostly routed! Added heatsink 3.3V version
2019-10-28 Board fully routed. Added test header
2019-10-28 Minimized board area to 4.5x3inches
2019-10-28 Moved mounting holes slighly
2019-10-28 Added ref-des and labels
2019-10-28 Fixed minor airwire issues
2019-10-28 Rotated 5VRegs so that Heatsink faces edge
2019-10-28 Moved some labels
2019-10-28 Added notes in schem
2019-10-30 Filled out MCU Board BOM. Nearly complete BOM except Passives
2019-11-02 Added PDFs of each schematic
2019-11-02 added design rules. Gave 12V to expansion board rather than 10V. Fixed traces near 3.3V reg.
2019-11-02 Added MG logo to bottom of board, as bRestrict
2019-11-02 Started backpack board
2019-11-02 Added components to library and schem
2019-11-02 Added more components
2019-11-02 Added analog circuitry. Most of schem is done. Still must do optoisolation and DIO protection
2019-11-02 Began board layout. Defined dimensions.
2019-11-03 Began op amp placement. Very rough
2019-11-03 Fixed acid trap issues
2019-11-04 Spec'd header part. Added DIO protection diodes and resistors. Significantly more routing done
2019-11-04 Rotated MCU to a 45
2019-11-04 More routing
2019-11-04 Moved sfuse so it does not block power jack
2019-11-04 Added toasty. Rotated Regs for heatsink on part sub
2019-11-04 added names
2019-11-04 Added DRU file from silverCircuits. Also Changed logo on bottom layer so that FR4 is used for logo
2019-11-04 Added revision label
2019-11-04 Exported BOM from eagle. Spec'd resistors
2019-11-04 Power jack changed
2019-11-04 Changed jack, again
2019-11-04 Added gerber files
2019-11-04 Added bKeepout logo
2019-11-04 New gerbers. Redid font
2019-11-04 Updated gerbers
2019-11-05 Added 2nd order filter to FGEN
2019-11-05 Did stuff
2019-11-08 worked on BOM. Added values to LED resistors.
2019-11-09 Finished backpack BOM. Nearly ready to order.
2019-11-09 Determined final qtys for ordering
2019-11-09 Hopefully fixed MBP/PSB mixup
2019-11-09 Changed 10nF capacitor
2019-11-09 Shrunk board to 3x3'' size
2019-11-09 Added optoisolators to library. Wired up. Still need to finish USB power circuit.
2019-11-10 Added usb power. Switched optocouplers to active-high
2019-11-10 Routed more traces
2019-11-11 Moved headers and holes
2019-11-11 Added stuff
2019-11-11 Added labels
2019-11-12 Added lasercut information
2019-11-12 Moved Bannana connectors. Added switch and LED labels
2019-11-12 Added vector font, box around meter controls
2019-11-17 Faceplate things
2019-11-18 BOM stuff
2019-11-18 Routed most traces
2019-11-18 Full layout complete. Added 9V to DIO header
2019-11-18 Added test points and labels
2019-11-18 Added attribution. Must add vertical USB port compatability.
2019-11-18 Added cdr and svg files
2019-11-19 Added vertical USB. Ready to purchase
2019-11-19 rerouted fgen and crystal as diff pair. Should be better for high frequency
2019-11-19 Finished routing FGEN, added option for DIO DDS or DAC powered FGEN
2019-11-19 Added gerbers
2022-02-16 Added pdf of schematic, added images

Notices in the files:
parts and their libraries:
SparkFun-Connectors: Licensing: Creative Commons ShareAlike 4.0 International - https://creativecommons.org/licenses/by-sa/4.0
